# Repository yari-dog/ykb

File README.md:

## PCB
using 
 - https://github.com/ebastler/marbastlib for choc and controller (0xCB helios) footprints

for whatever reason, the GC9A01 board that i've designed this around uses i2c names instead of spi names, however it does indeed use spi. I've chosen to use the labels printed on the solder mask of the LCD as opposed to the correct SPI ones.

# thanks to pat for double checking my work lmao

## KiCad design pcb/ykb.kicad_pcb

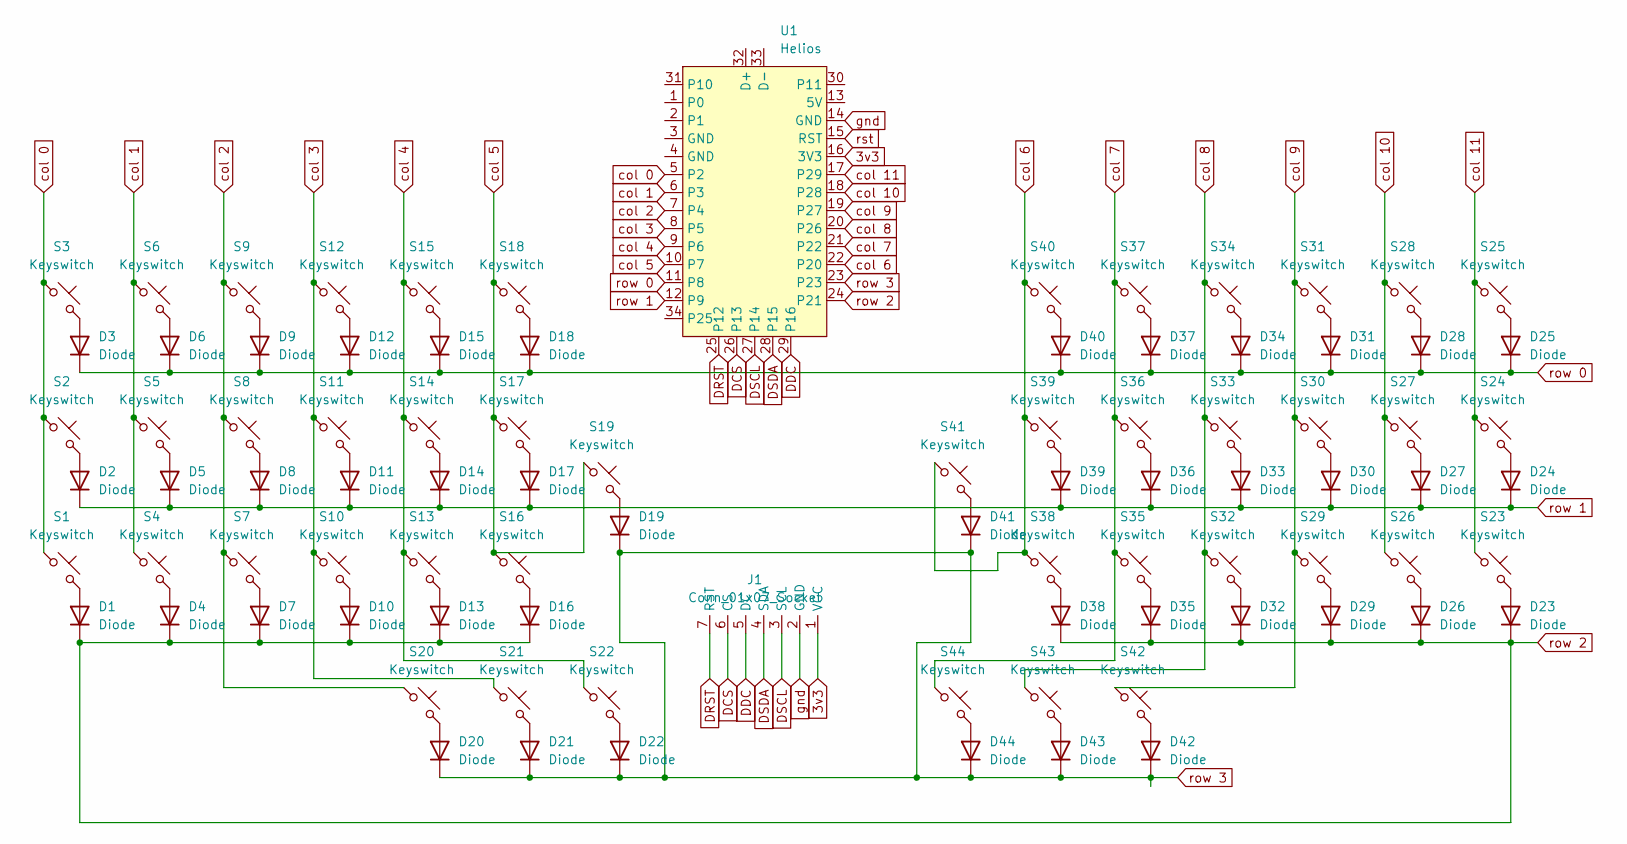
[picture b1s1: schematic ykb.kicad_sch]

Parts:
D1, D2, D3, D4, D5, D6, D7, D8, D9, D10, D11, D12, D13, D14, D15, D16, D17, D18, D19, D20, D21, D22, D23, D24, D25, D26, D27, D28, D29, D30, D31, D32, D33, D34, D35, D36, D37, D38, D39, D40, D41, D42, D43, D44: Diode; Diode_SOD-123
J1: Conn_01x07_Socket; PinHeader_1x07_P2.54mm_Vertical
S1, S2, S3, S4, S5, S6, S7, S8, S9, S10, S11, S12, S13, S14, S15, S16, S17, S18, S19, S20, S21, S22, S23, S24, S25, S26, S27, S28, S29, S30, S31, S32, S33, S34, S35, S36, S37, S38, S39, S40, S41, S42, S43, S44: Keyswitch; Hotswap_Choc_V1V2_1.00u
U1: Helios; Helios_AC

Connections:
3v3: J1.1 (VCC), U1.16 (3V3)
DCS: J1.6 (CS), U1.26 (P13)
DDC: J1.5 (DC), U1.29 (P16)
DRST: J1.7 (RST), U1.25 (P12)
DSCL: J1.3 (SCL), U1.27 (P14)
DSDA: J1.4 (SDA), U1.28 (P15)
unnamed: D1.2 (A), S1.2
unnamed: D2.2 (A), S2.2
unnamed: D3.2 (A), S3.2
unnamed: D4.2 (A), S4.2
unnamed: D5.2 (A), S5.2
unnamed: D6.2 (A), S6.2
unnamed: D7.2 (A), S7.2
unnamed: D8.2 (A), S8.2
unnamed: D9.2 (A), S9.2
unnamed: D10.2 (A), S10.2
unnamed: D11.2 (A), S11.2
unnamed: D12.2 (A), S12.2
unnamed: D13.2 (A), S13.2
unnamed: D14.2 (A), S14.2
unnamed: D15.2 (A), S15.2
unnamed: D16.2 (A), S16.2
unnamed: D17.2 (A), S17.2
unnamed: D18.2 (A), S18.2
unnamed: D19.2 (A), S19.2
unnamed: D20.2 (A), S20.2
unnamed: D21.2 (A), S21.2
unnamed: D22.2 (A), S22.2
unnamed: D23.2 (A), S23.2
unnamed: D24.2 (A), S24.2
unnamed: D25.2 (A), S25.2
unnamed: D26.2 (A), S26.2
unnamed: D27.2 (A), S27.2
unnamed: D28.2 (A), S28.2
unnamed: D29.2 (A), S29.2
unnamed: D30.2 (A), S30.2
unnamed: D31.2 (A), S31.2
unnamed: D32.2 (A), S32.2
unnamed: D33.2 (A), S33.2
unnamed: D34.2 (A), S34.2
unnamed: D35.2 (A), S35.2
unnamed: D36.2 (A), S36.2
unnamed: D37.2 (A), S37.2
unnamed: D38.2 (A), S38.2
unnamed: D39.2 (A), S39.2
unnamed: D40.2 (A), S40.2
unnamed: D41.2 (A), S41.2
unnamed: D42.2 (A), S42.2
unnamed: D43.2 (A), S43.2
unnamed: D44.2 (A), S44.2
col 0: S1.1, S2.1, S3.1, U1.5 (P2)
col 1: S4.1, S5.1, S6.1, U1.6 (P3)
col 2: S7.1, S8.1, S9.1, S20.1, U1.7 (P4)
col 3: S10.1, S11.1, S12.1, S21.1, U1.8 (P5)
col 4: S13.1, S14.1, S15.1, S22.1, U1.9 (P6)
col 5: S16.1, S17.1, S18.1, S19.1, U1.10 (P7)
col 6: S38.1, S39.1, S40.1, S41.1, U1.22 (P20)
col 7: S35.1, S36.1, S37.1, S44.1, U1.21 (P22)
col 8: S32.1, S33.1, S34.1, S43.1, U1.20 (P26)
col 9: S29.1, S30.1, S31.1, S42.1, U1.19 (P27)
col 10: S26.1, S27.1, S28.1, U1.18 (P28)
col 11: S23.1, S24.1, S25.1, U1.17 (P29)
gnd: J1.2 (GND), U1.14 (GND)
row 0: D3.1 (K), D6.1 (K), D9.1 (K), D12.1 (K), D15.1 (K), D18.1 (K), D25.1 (K), D28.1 (K), D31.1 (K), D34.1 (K), D37.1 (K), D40.1 (K), U1.11 (P8)
row 1: D2.1 (K), D5.1 (K), D8.1 (K), D11.1 (K), D14.1 (K), D17.1 (K), D24.1 (K), D27.1 (K), D30.1 (K), D33.1 (K), D36.1 (K), D39.1 (K), U1.12 (P9)
row 2: D1.1 (K), D4.1 (K), D7.1 (K), D10.1 (K), D13.1 (K), D16.1 (K), D23.1 (K), D26.1 (K), D29.1 (K), D32.1 (K), D35.1 (K), D38.1 (K), U1.24 (P21)
row 3: D19.1 (K), D20.1 (K), D21.1 (K), D22.1 (K), D41.1 (K), D42.1 (K), D43.1 (K), D44.1 (K), U1.23
rst: U1.15 (RST)

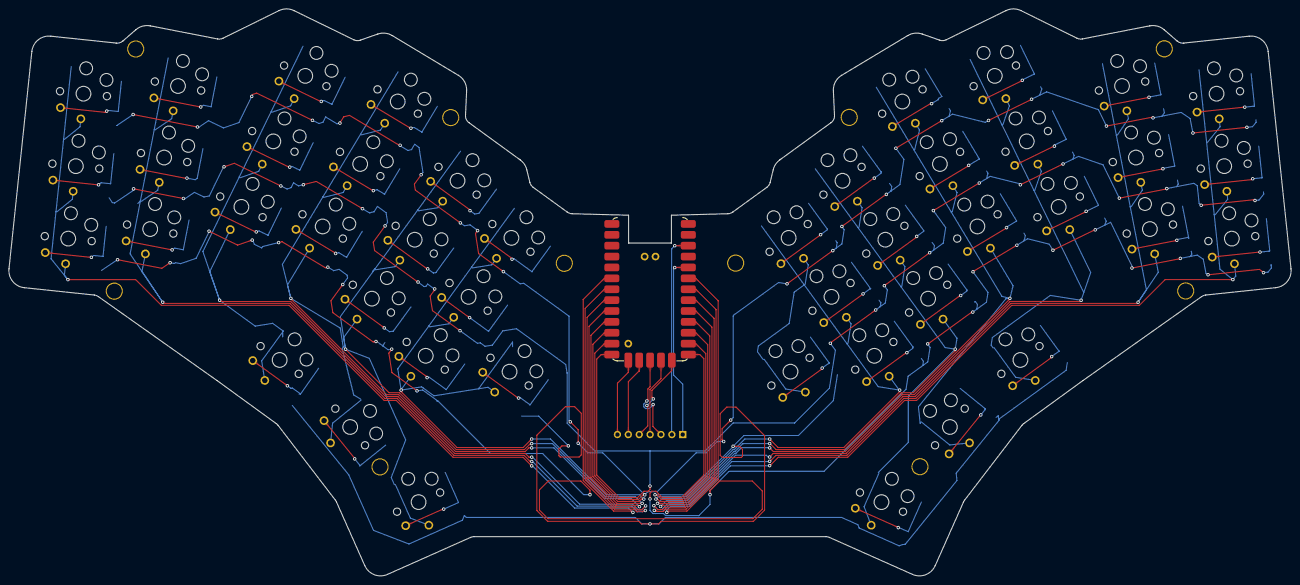
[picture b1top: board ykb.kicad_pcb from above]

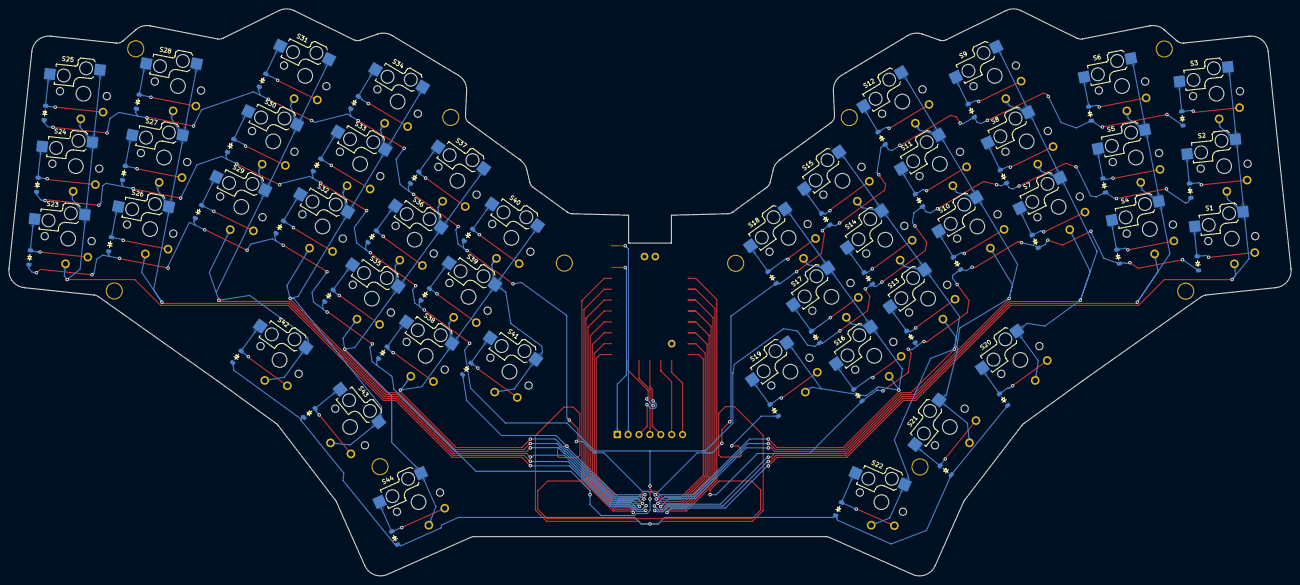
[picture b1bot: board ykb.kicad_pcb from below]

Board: 2 copper layers, 299.2 x 132.3 mm, 90 parts (44 on the bottom side), 67 nets.

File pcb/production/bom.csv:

Designator,Footprint,Quantity,Value,LCSC Part #
"_10, _9, _8, _7, _6, _5, _4, _3, _2, ",,10,,
"D1, D10, D11, D12, D13, D14, D15, D16, D17, D18, D19, D2, D20, D21, D22, D23, D24, D25, D26, D27, D28, D29, D3, D30, D31, D32, D33, D34, D35, D36, D37, D38, D39, D4, D40, D41, D42, D43, D44, D5, D6, D7, D8, D9",Diode_SOD-123,44,Diode,
J1,PinHeader_1x07_P2.54mm_Vertical,1,Conn_01x07_Socket,
"S1, S10, S11, S12, S13, S14, S15, S16, S17, S18, S19, S2, S20, S21, S22, S23, S24, S25, S26, S27, S28, S29, S3, S30, S31, S32, S33, S34, S35, S36, S37, S38, S39, S4, S40, S41, S42, S43, S44, S5, S6, S7, S8, S9",Hotswap_Choc_V1V2_1.00u,44,Keyswitch,

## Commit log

2024-06-15 init, empty pcb files
2024-06-15 gitignore and ergogen yaml
2024-06-15 fixev git ignore location lmao
2024-06-15 fixed goofy shit with the thumb cluster
2024-06-16 proper footprints and s/d connections made
2024-06-16 switched to castlated controller :3
2024-06-16 switched splay from key units to degrees because i did key units for some reason
2024-06-16 fixed cut
2024-06-16 fixed model refs, placed all diodes
2024-06-16 lcd footprint and started routing
2024-06-16 further routing
2024-06-16 even more routing
2024-06-17 reset row-controller routing, centered things better
2024-06-17 column trace highway
2024-06-17 fixed incorrect net assignment
2024-06-17 finished routing
2024-06-20 all done other than mounting holes :3
2024-06-21 fixed lcd and some design rule errors
2024-06-21 chilled out the routing a little bit lmao
2024-06-21 slight touch-up of display tracks
2024-06-21 diodes on right side
2024-06-21 ideally, finalised routing
2024-06-21 teardrops on pads
2024-06-21 plate started, standoff holes placed
2024-06-21 plate :3
2024-06-21 done
2024-06-26 case :3
2024-06-27 some exports so i can print a case lmao
2024-06-28 fixed rebase
2024-06-28 bro git fucked my shit up
